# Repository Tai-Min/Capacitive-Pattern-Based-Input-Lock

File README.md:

#  Capacitive Pattern Based Input Lock

Created for [Propel Human-Machine Interactions into the Future
with Infineon](https://www.hackster.io/contests/capsense). For the detailed description of the project see [Capacitive Pattern Based Input Lock on Hackster.io](https://www.hackster.io/Tai-Min/capacitive-pattern-based-input-lock-50ced4)

## Folder structure
* case - Simple stand made in FreeCAD (FCStd and STL files)
* code
    * network - Files for gathering dataset, training the network and creating C++ header file for custom inference engine as well as some debug code
    * psoc4100s - Source code for the PSoC 4100S PIONEER KIT
    * scripts - Some code used in Hackster article
* graphics - Custom graphics for front panel of the kit made in GIMP
* shield - KiCad files for custom PCB with relays and diodes

## Instructions
### PCB
Use KiCad's 3D viewer, PCB viewer and bill of materials to assembly the PCB and attach it to the back of the kit via Arduino headers.

### How to run the code
Simply open the project in PSoC Creator 4.0 and upload it to the device.

### How to use custom network model
1. In kit's source code, in helpers.hpp comment out
    * #define INFOS
    * #define WARNS
    * #define DBGS
2. In kit's main.cpp uncomment 
    * //#define SKIP_ADD_PATTERN
    * //#define PRINT_RAW_BUFFER
3. Compile and upload edited code
4. In network/collector.py change label to string of your choice and serial port to kit's port
5. Run collectors.py and collect as many samples of given label as needed. To collect a sample:
    * Draw something on the panel
    * Press accept button
6. Repeat for all needed labels
7. In network/model.py change training constants and model's structure as needed and run the script
8. Replace kit's ssie_model.hpp with content of C++ output of the script 
9. Restore defines in 1. and 2.
10. Compile and upload the code to the device

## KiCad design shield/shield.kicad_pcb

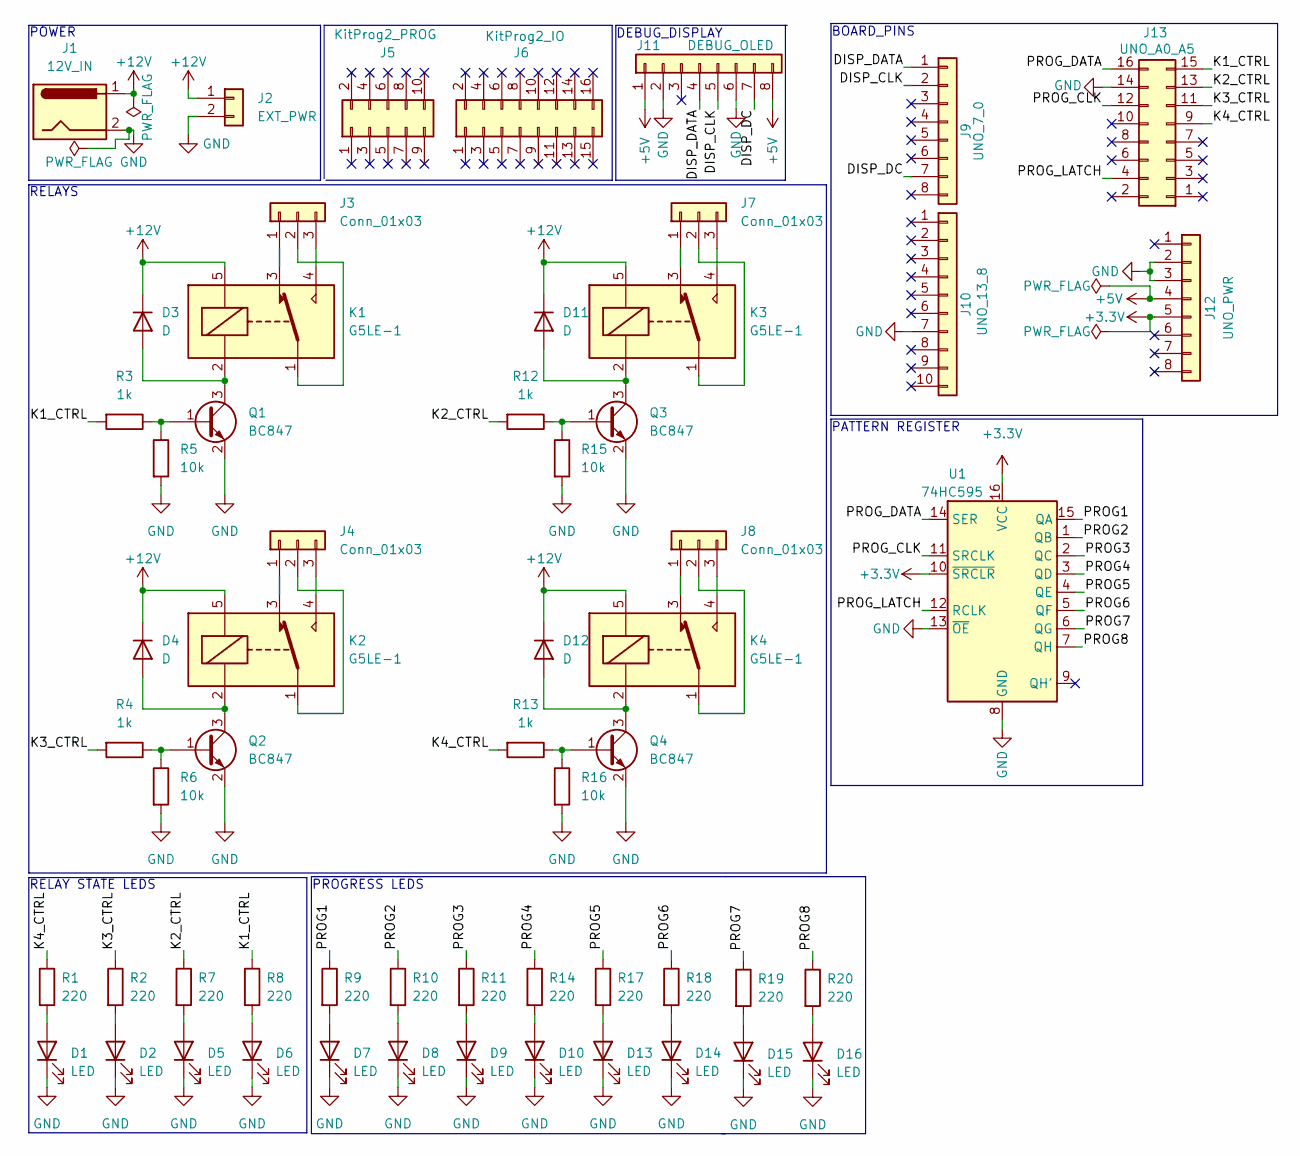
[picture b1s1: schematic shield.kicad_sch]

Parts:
D1, D2, D5, D6, D7, D8, D9, D10, D13, D14, D15, D16: LED; LED_1206_3216Metric_Pad1.42x1.75mm_HandSolder
D3, D4, D11, D12: D; D_SMC_Handsoldering
J1: 12V_IN; BarrelJack_Horizontal
J2: EXT_PWR; PinHeader_1x02_P2.54mm_Vertical
J3, J4, J7, J8: Conn_01x03; TerminalBlock_Phoenix_MKDS-1,5-3-5.08_1x03_P5.08mm_Horizont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
J5: KitProg2_PROG; PinHeader_2x05_P2.54mm_Vertical
J6: KitProg2_IO; PinHeader_2x08_P2.54mm_Vertical
J9: UNO_7_0; PinHeader_1x08_P2.54mm_Vertical
J10: UNO_13_8; PinHeader_1x10_P2.54mm_Vertical
J11: DEBUG_OLED; PinSocket_1x08_P2.54mm_Vertical
J12: UNO_PWR; PinHeader_1x08_P2.54mm_Vertical
J13: UNO_A0_A5; PinHeader_2x08_P2.54mm_Vertical
K1, K2, K3, K4: G5LE-1; Relay_SPDT_Omron-G5LE-1
Q1, Q2, Q3, Q4: BC847; TSOT-23
R1, R2, R7, R8, R9, R10, R11, R14, R17, R18, R19, R20: 220; R_1206_3216Metric_Pad1.30x1.75mm_HandSolder
R3, R4, R12, R13: 1k; R_1206_3216Metric_Pad1.30x1.75mm_HandSolder
R5, R6, R15, R16: 10k; R_1206_3216Metric_Pad1.30x1.75mm_HandSolder
U1: 74HC595; SOP-16_4.55x10.3mm_P1.27mm

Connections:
+3.3V: J12.5, U1.10 (~SRCLR), U1.16 (VCC)
+5V: J11.1, J11.8, J12.4
+12V: D3.1 (K), D4.1 (K), D11.1 (K), D12.1 (K), J1.1, J2.1, K1.5, K2.5, K3.5, K4.5
/DISP_CLK: J9.2, J11.5
/DISP_DATA: J9.1, J11.4
/DISP_DC: J9.7, J11.7
/K1_CTRL: J13.15, R3.2, R8.1
/K2_CTRL: J13.13, R7.1, R12.2
/K3_CTRL: J13.11, R2.1, R4.2
/K4_CTRL: J13.9, R1.1, R13.2
/PROG1: R9.1, U1.15 (QA)
/PROG2: R10.1, U1.1 (QB)
/PROG3: R11.1, U1.2 (QC)
/PROG4: R14.1, U1.3 (QD)
/PROG5: R17.1, U1.4 (QE)
/PROG6: R18.1, U1.5 (QF)
/PROG7: R19.1, U1.6 (QG)
/PROG8: R20.1, U1.7 (QH)
/PROG_CLK: J13.12, U1.11 (SRCLK)
/PROG_DATA: J13.16, U1.14 (SER)
/PROG_LATCH: J13.4, U1.12 (RCLK)
GND: D1.1 (K), D2.1 (K), D5.1 (K), D6.1 (K), D7.1 (K), D8.1 (K), D9.1 (K), D10.1 (K), D13.1 (K), D14.1 (K), D15.1 (K), D16.1 (K), J1.2, J2.2, J10.7, J11.2, J11.6, J12.2, J12.3, J13.14, Q1.2 (E), Q2.2 (E), Q3.2 (E), Q4.2 (E), R5.2, R6.2, R15.2, R16.2, U1.8 (GND), U1.13 (~OE)
unnamed: D1.2 (A), R1.2
unnamed: D2.2 (A), R2.2
unnamed: D3.2 (A), K1.2, Q1.3 (C)
unnamed: D4.2 (A), K2.2, Q2.3 (C)
unnamed: D5.2 (A), R7.2
unnamed: D6.2 (A), R8.2
unnamed: D7.2 (A), R9.2
unnamed: D8.2 (A), R10.2
unnamed: D9.2 (A), R11.2
unnamed: D10.2 (A), R14.2
unnamed: D11.2 (A), K3.2, Q3.3 (C)
unnamed: D12.2 (A), K4.2, Q4.3 (C)
unnamed: D13.2 (A), R17.2
unnamed: D14.2 (A), R18.2
unnamed: D15.2 (A), R19.2
unnamed: D16.2 (A), R20.2
unnamed: J3.1, K1.3
unnamed: J3.2, K1.1
unnamed: J3.3, K1.4
unnamed: J4.1, K2.3
unnamed: J4.2, K2.1
unnamed: J4.3, K2.4
unnamed: J7.1, K3.3
unnamed: J7.2, K3.1
unnamed: J7.3, K3.4
unnamed: J8.1, K4.3
unnamed: J8.2, K4.1
unnamed: J8.3, K4.4
unnamed: Q1.1 (B), R3.1, R5.1
unnamed: Q2.1 (B), R4.1, R6.1
unnamed: Q3.1 (B), R12.1, R15.1
unnamed: Q4.1 (B), R13.1, R16.1

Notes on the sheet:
BOARD_PINS
PATTERN REGISTER
POWER
RELAYS
PROGRESS LEDS
RELAY STATE LEDS
DEBUG_DISPLAY

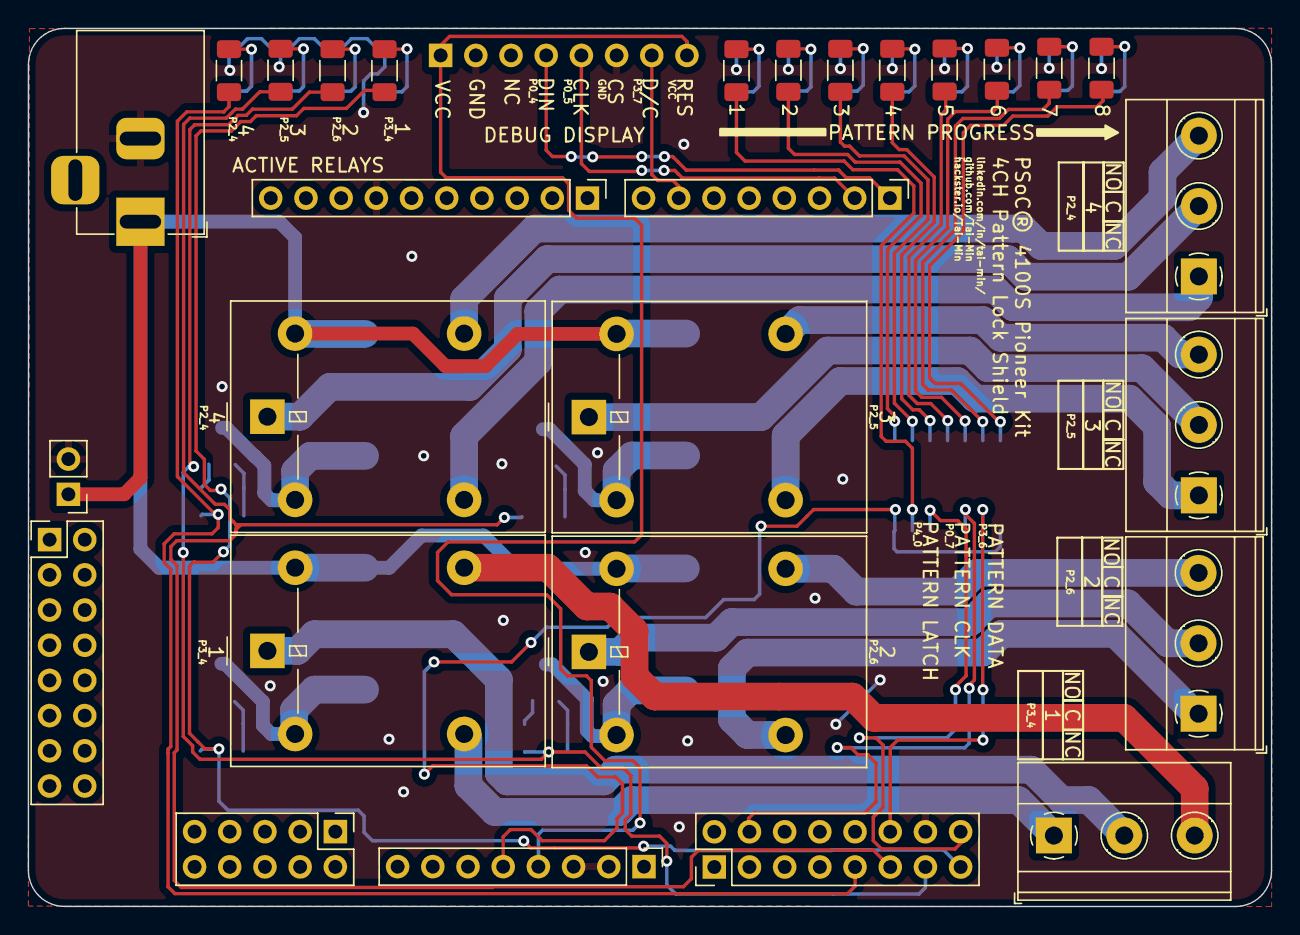
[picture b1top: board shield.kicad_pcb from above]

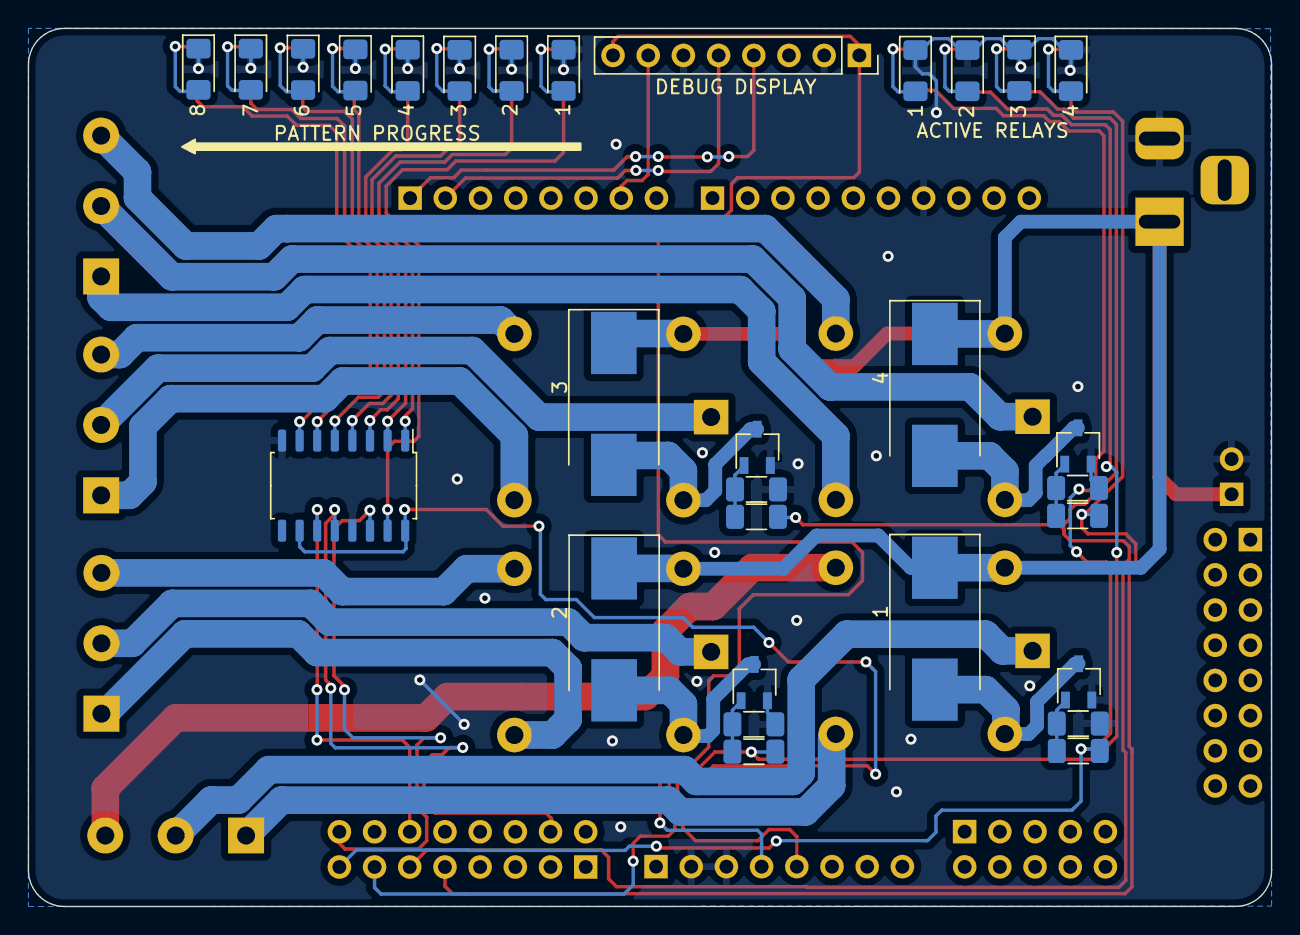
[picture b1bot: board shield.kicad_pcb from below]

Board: 2 copper layers, 89.7 x 63.4 mm, 58 parts (30 on the bottom side), 54 nets.

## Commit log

2023-02-21 Add working relays, add pattern changing script
2023-02-28 Polish neural network engine
2023-02-28 Add README.md
2023-02-28 Move README.md
2023-02-28 Add image
